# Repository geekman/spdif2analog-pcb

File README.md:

SPDIF Optical to Analog Converter
==================================

This is a device that converts uncompressed PCM audio stream from an OPTICAL
OUT connection into analog audio that can be connected to a LINE IN of some
device.
It does NOT support decoding 5.1 audio streams.

Design considerations and other details were written up in a blog post here: 
<https://irq5.io/2011/03/10/optical-to-analog-audio-converter/>

Files
------

The hardware design files are in the *CadSoft EAGLE* format, 
now known as [Autodesk EAGLE](https://www.autodesk.com/products/eagle/overview).
You can download and use EAGLE for free to open the files, view the schematics 
and generate Gerber files for manufacture.

For convenience, generated files _may_ have been made available under the 
**Releases** or **Downloads** section of the repository, but otherwise, 
you have to do it yourself.

Some footprints used in the design may have come from the 
[SparkFun EAGLE libraries](https://github.com/sparkfun/SparkFun-Eagle-Libraries).

License
--------

**spdif2analog is licensed under the TAPR Open Hardware License (https://www.tapr.org/OHL).**

Copyright (C) 2011 Darell Tan

The TAPR Open Hardware License ("OHL") agreement provides a legal
framework for Open Hardware projects.
The OHL addresses unique issues involved in the creation of tangible,
physical things, but does not cover software, firmware, or code loaded
into programmable devices.
While the terms and conditions of the License take precedence, here are some
key points, provided solely for convenience:

*  You may modify the documentation and make products based upon it.

*  You may use products for any legal purpose without limitation.

*  You may distribute products you make to third parties, if you either
   include the documentation on which the product is based, or make it
   available without charge for at least three years to anyone who requests
   it.

*  You may distribute unmodified documentation, but you must include the
   complete package as you received it.

*  You may distribute modified documentation or products based on it, if you 
   license your modifications under the OHL and include those modifications.

*  Any time the OHL requires you to make documentation available to
   others, you must include all the materials you received from the
   upstream licensors.  In addition, if you have modified the
   documentation, you must identify the modifications in a text file,
   and include any new files you created.

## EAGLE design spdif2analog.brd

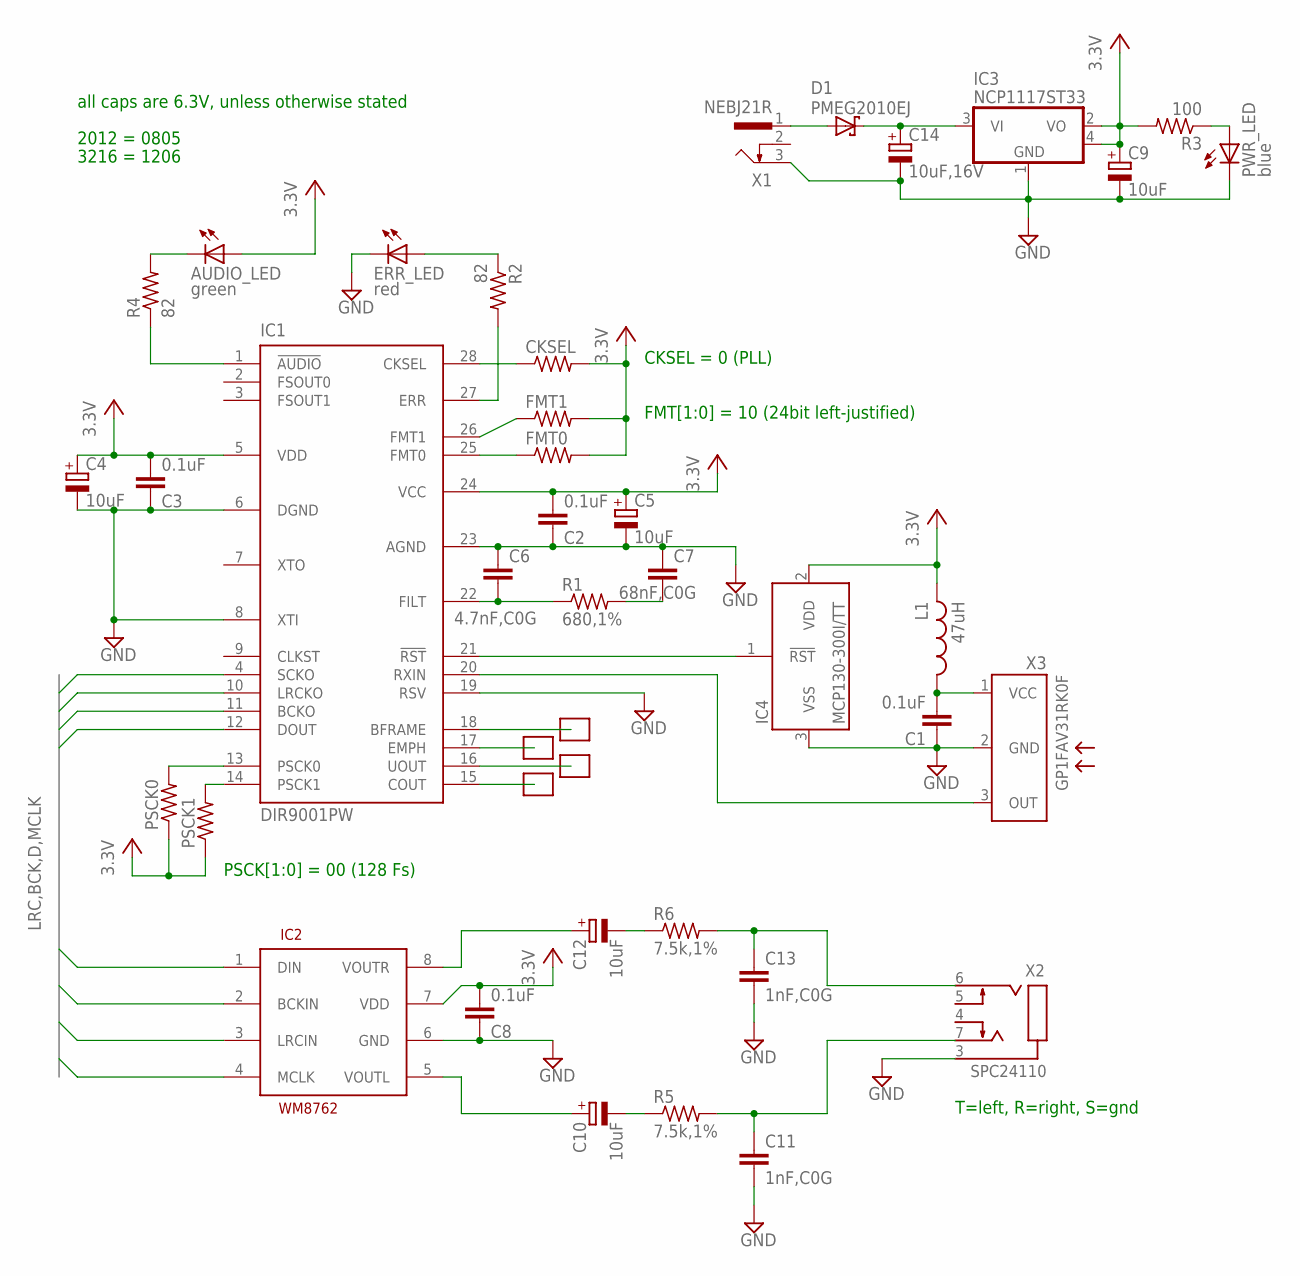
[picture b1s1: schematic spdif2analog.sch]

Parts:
AUDIO_LED: green; CHIPLED_0805
C1, C2, C3, C8: 0.1uF; C0805
C4, C5, C9, C10, C12: 10uF; A/3216-18R
C6: 4.7nF,C0G; C0805
C7: 68nF,C0G; C025_050-035X075
C11, C13: 1nF,C0G; C0805
C14: 10uF,16V; A/3216-18R
CKSEL: 5.1k; R0805
D1: PMEG2010EJ; SOD-323
ERR_LED: red; CHIPLED_0805
FMT0, FMT1: 5.1k; R0805
IC1: DIR9001PW; PW_R-PDSO-G28
IC2: WM8762; SOIC8
IC3: NCP1117ST33; SOT-223
IC4: MCP130-300I/TT; SOT-23-3
L1: 47uH; L2012C
PSCK0, PSCK1: 5.1k; R0805
PWR_LED: blue; CHIPLED_0805
R1: 680,1%; R0805
R2, R4: 82; R0805
R3: 100; R0805
R5, R6: 7.5k,1%; R0805
U$1, U$2, U$3, U$4: PAD.015
X1: NEBJ21R
X2: SPC24110
X3: GP1FAV31RK0F

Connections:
3.3V: AUDIO_LED.A, C2.2, C3.2, C4.+, C5.+, C8.2, C9.+, CKSEL.2, FMT0.2, FMT1.2, IC1.5 (VDD), IC1.24 (VCC), IC2.7 (VDD), IC3.2 (VO), IC3.4 (TAB), IC4.2 (VDD), L1.2, PSCK0.1, PSCK1.1, R3.2
BCK: IC1.11 (BCKO), IC2.2 (BCKIN)
D: IC1.12 (DOUT), IC2.1 (DIN)
GND: C1.1, C2.1, C3.1, C4.-, C5.-, C6.1, C7.1, C8.1, C9.-, C11.2, C13.2, C14.-, ERR_LED.C, IC1.6 (DGND), IC1.8 (XTI), IC1.19 (RSV), IC1.23 (AGND), IC2.6 (GND), IC3.1 (GND), IC4.3 (VSS), PWR_LED.C, X1.3, X2.3 (SLEEVE), X3.2 (GND)
LRC: IC1.10 (LRCKO), IC2.3 (LRCIN)
MCLK: IC1.4 (SCKO), IC2.4 (MCLK)
unnamed: C1.2, L1.1, X3.1 (VCC)
unnamed: IC1.21 (!RST), IC4.1 (!RST)
unnamed: C7.2, R1.2
unnamed: IC1.20 (RXIN), X3.3 (OUT)
unnamed: C6.2, IC1.22 (FILT), R1.1
unnamed: IC1.13 (PSCK0), PSCK0.2
unnamed: D1.2 (A), X1.1
unnamed: IC1.14 (PSCK1), PSCK1.2
unnamed: FMT1.1, IC1.26 (FMT1)
unnamed: FMT0.1, IC1.25 (FMT0)
unnamed: CKSEL.1, IC1.28 (CKSEL)
unnamed: ERR_LED.A, R2.1
unnamed: IC1.27 (ERR), R2.2
unnamed: C10.+, IC2.5 (VOUTL)
unnamed: PWR_LED.A, R3.1
unnamed: C12.+, IC2.8 (VOUTR)
unnamed: C13.1, R6.2, X2.6 (RING)
unnamed: C11.1, R5.2, X2.7 (TIP)
unnamed: IC1.18 (BFRAME), U$1.1
unnamed: IC1.17 (EMPH), U$2.1
unnamed: IC1.16 (UOUT), U$3.1
unnamed: IC1.15 (COUT), U$4.1
unnamed: AUDIO_LED.C, R4.2
unnamed: C12.-, R6.1
unnamed: IC1.1 (!AUDIO), R4.1
unnamed: C14.+, D1.1 (C), IC3.3 (VI)
unnamed: C10.-, R5.1

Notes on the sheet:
2012 = 0805
3216 = 1206
FMT[1:0] = 10 (24bit left-justified)
PSCK[1:0] = 00 (128 Fs)
T=left, R=right, S=gnd
all caps are 6.3V, unless otherwise stated
CKSEL = 0 (PLL)

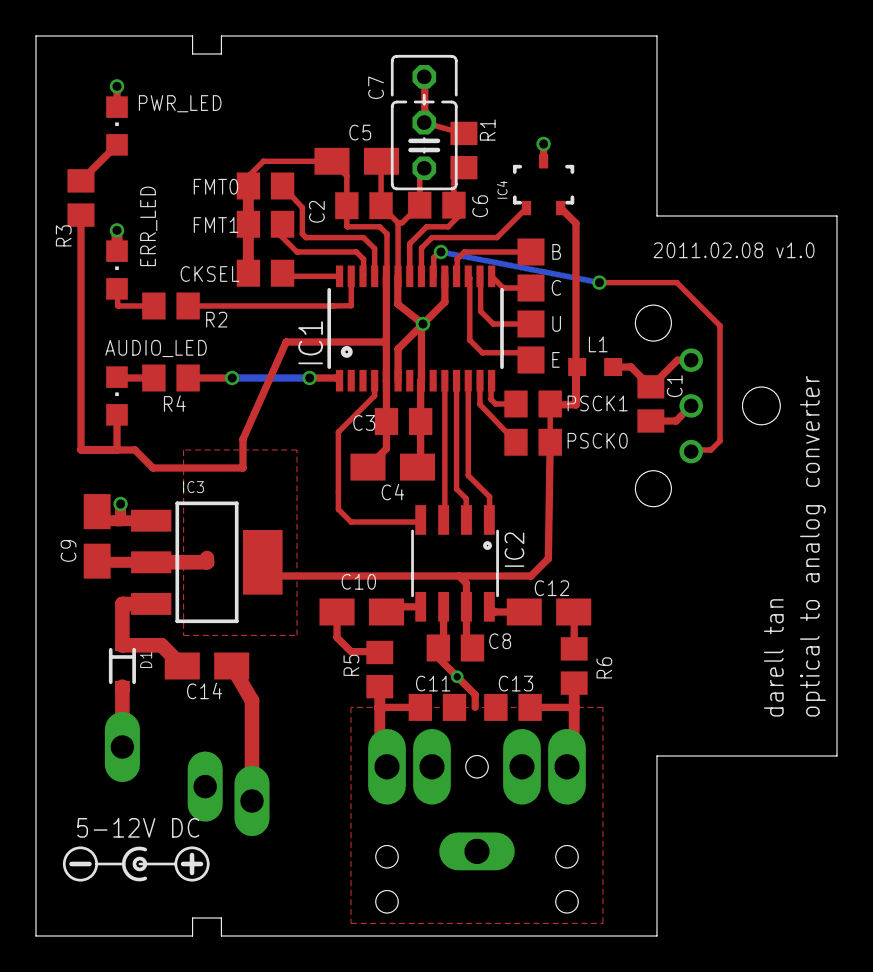
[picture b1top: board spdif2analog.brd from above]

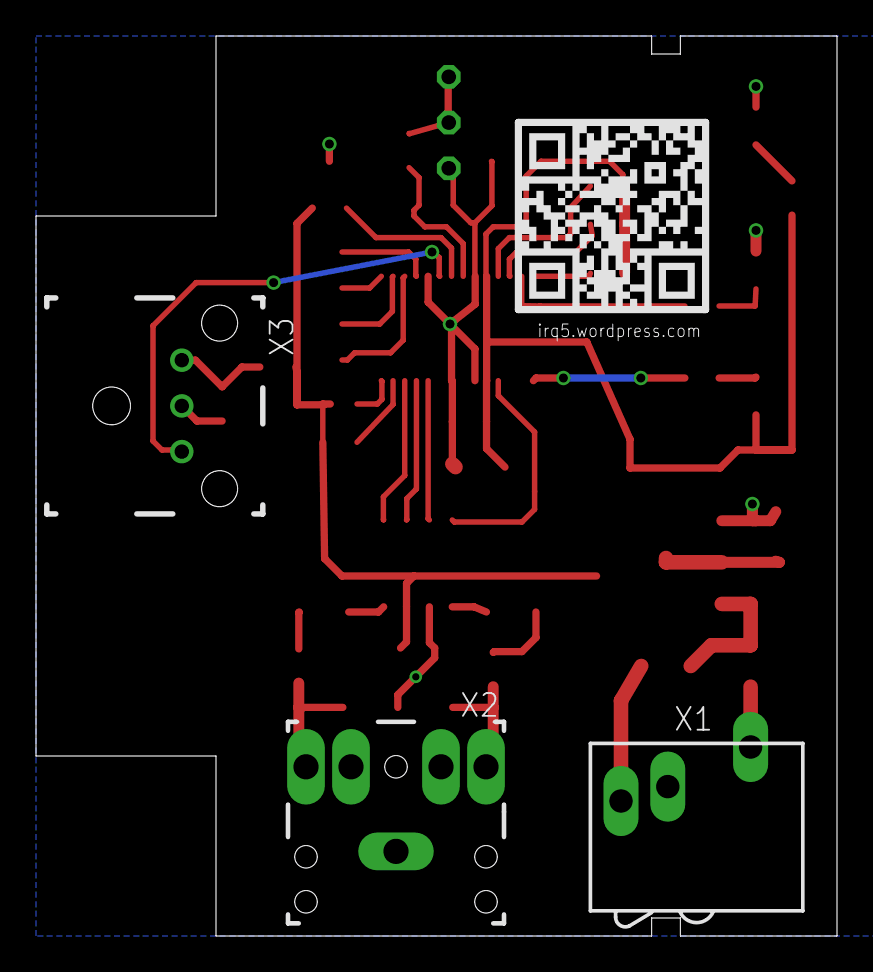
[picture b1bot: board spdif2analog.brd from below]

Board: 2 copper layers, 44.5 x 50.0 mm, 43 parts (4 on the bottom side), 33 nets.

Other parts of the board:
U$5: SILK-IRQ5_QR_CODE
U$6: 5-12V DC; SILK-DC_JACK_POL_A

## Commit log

2019-06-25 "Initial" commit.
